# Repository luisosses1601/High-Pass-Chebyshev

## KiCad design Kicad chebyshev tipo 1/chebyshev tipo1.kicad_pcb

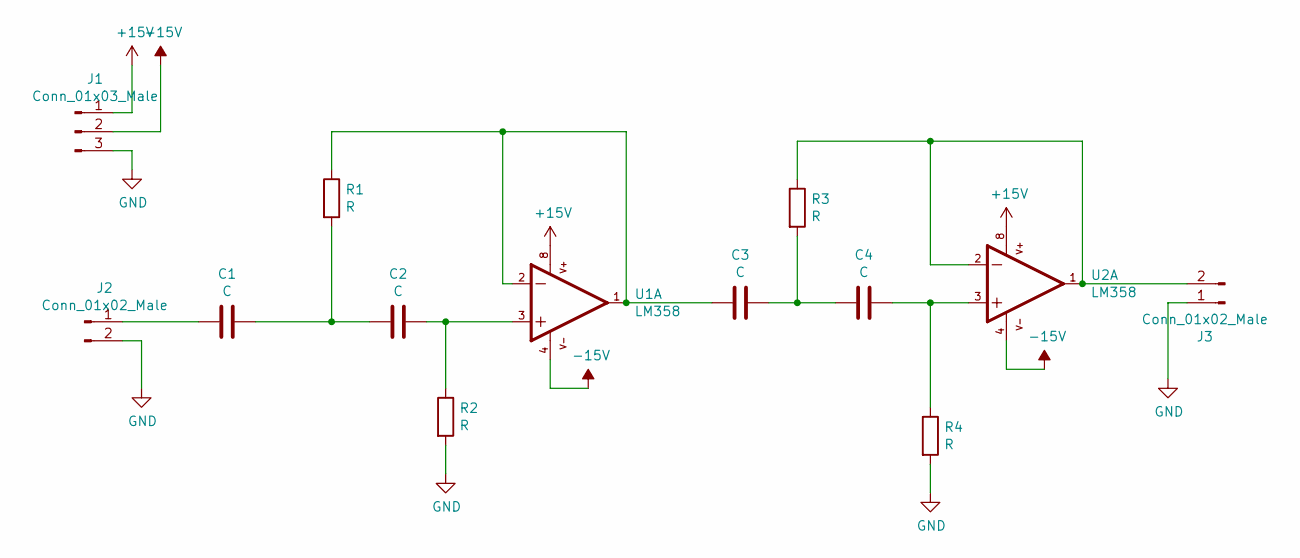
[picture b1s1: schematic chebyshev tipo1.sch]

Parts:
C1, C2, C3, C4: C; C_0805_2012Metric
J1: Conn_01x03_Male; PinHeader_1x03_P2.54mm_Vertical
J2, J3: Conn_01x02_Male; PinHeader_1x02_P2.54mm_Vertical
R1, R2, R3, R4: R; R_0805_2012Metric
U1, U2: LM358; DIP-8_W7.62mm

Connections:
+15V: J1.1, U1.8 (V+), U2.8 (V+)
-15V: J1.2, U1.4 (V-), U2.4 (V-)
GND: J1.3, J2.2, J3.1, R2.2, R4.2
unnamed: C1.1, C2.2, R1.2
unnamed: C1.2, J2.1
unnamed: C2.1, R2.1, U1.3 (+IN)
unnamed: C3.1, C4.2, R3.2
unnamed: C3.2, R1.1, U1.1 (OUT), U1.2 (-IN)
unnamed: C4.1, R4.1, U2.3 (+IN)
unnamed: J3.2, R3.1, U2.1 (OUT), U2.2 (-IN)

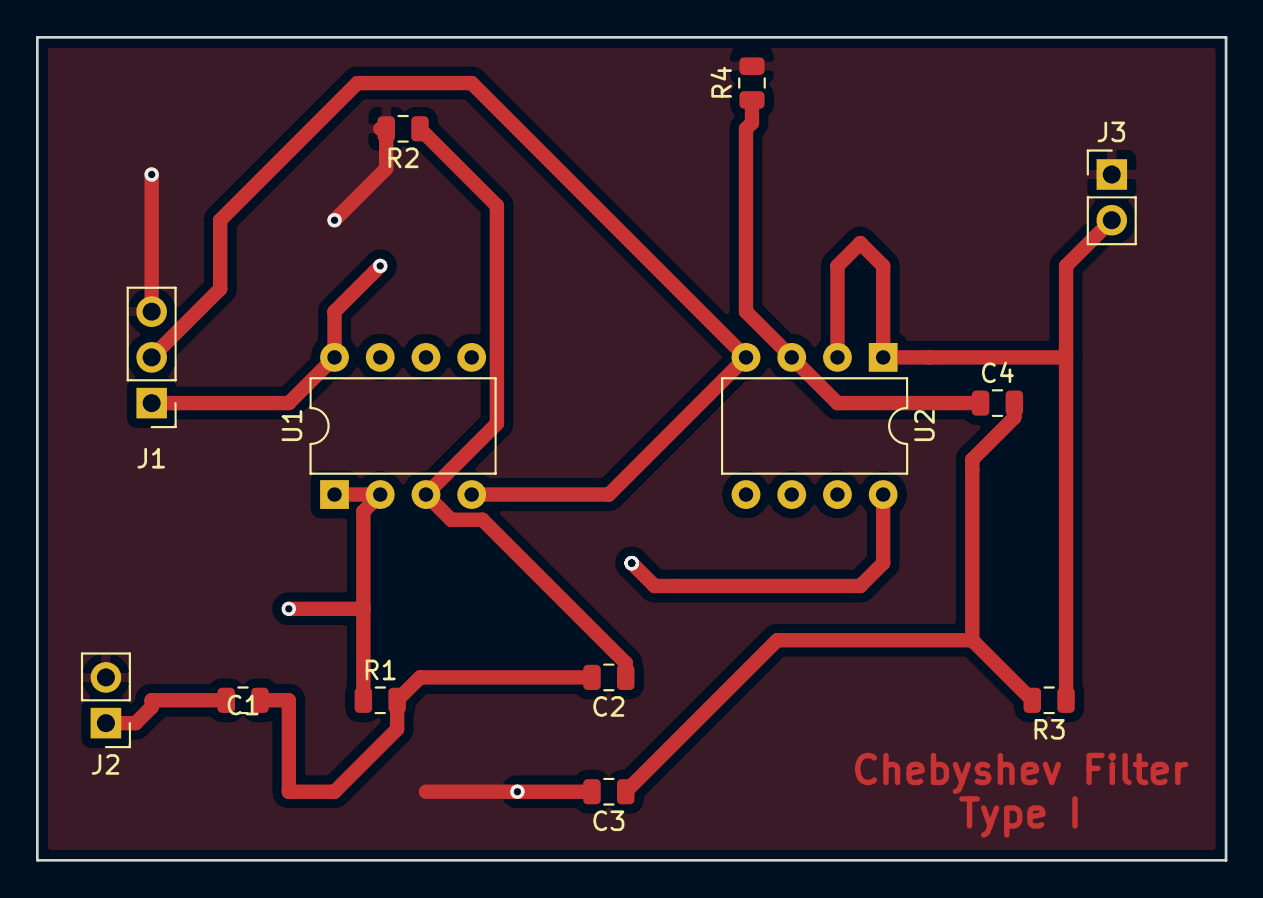
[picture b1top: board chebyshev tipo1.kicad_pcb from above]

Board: 2 copper layers, 66.0 x 45.7 mm, 13 parts (0 on the bottom side), 10 nets.

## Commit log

2019-03-11 Chebyshev High Pass
2019-03-13 Informe reducido, solo simulaciones poco calculo
